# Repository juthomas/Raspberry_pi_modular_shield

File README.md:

# Raspberry Pi hat for modular synthesizer input

## Schematics

- [Link to pdf](https://github.com/juthomas/Raspberry_pi_modular_shield/blob/master/Schematics%20PDF/Modular_Shield.pdf)

## Bill Of Materials

- [Link to IBOM](https://juthomas.github.io/Raspberry_pi_modular_shield/)

## Components

- [10K Resistors](https://www.lcsc.com/product-detail/Chip-Resistor-Surface-Mount_UNI-ROYAL-Uniroyal-Elec-0603WAF1002T5E_C25804.html) C25804

- [Zener Diodes](https://www.lcsc.com/product-detail/Zener-Diodes_onsemi-SZMM5Z6V8T1G_C894569.html) C894569

- [MCP3008](https://www.lcsc.com/product-detail/Analog-To-Digital-Converters-ADCs_Microchip-Tech-MCP3008-I-SL_C1520159.html) C1520159

## Install dependency for C coding

[spidev-lib](https://github.com/juthomas/spidev-lib)

dont forget to add the `-lspidev-lib` flag when compiling

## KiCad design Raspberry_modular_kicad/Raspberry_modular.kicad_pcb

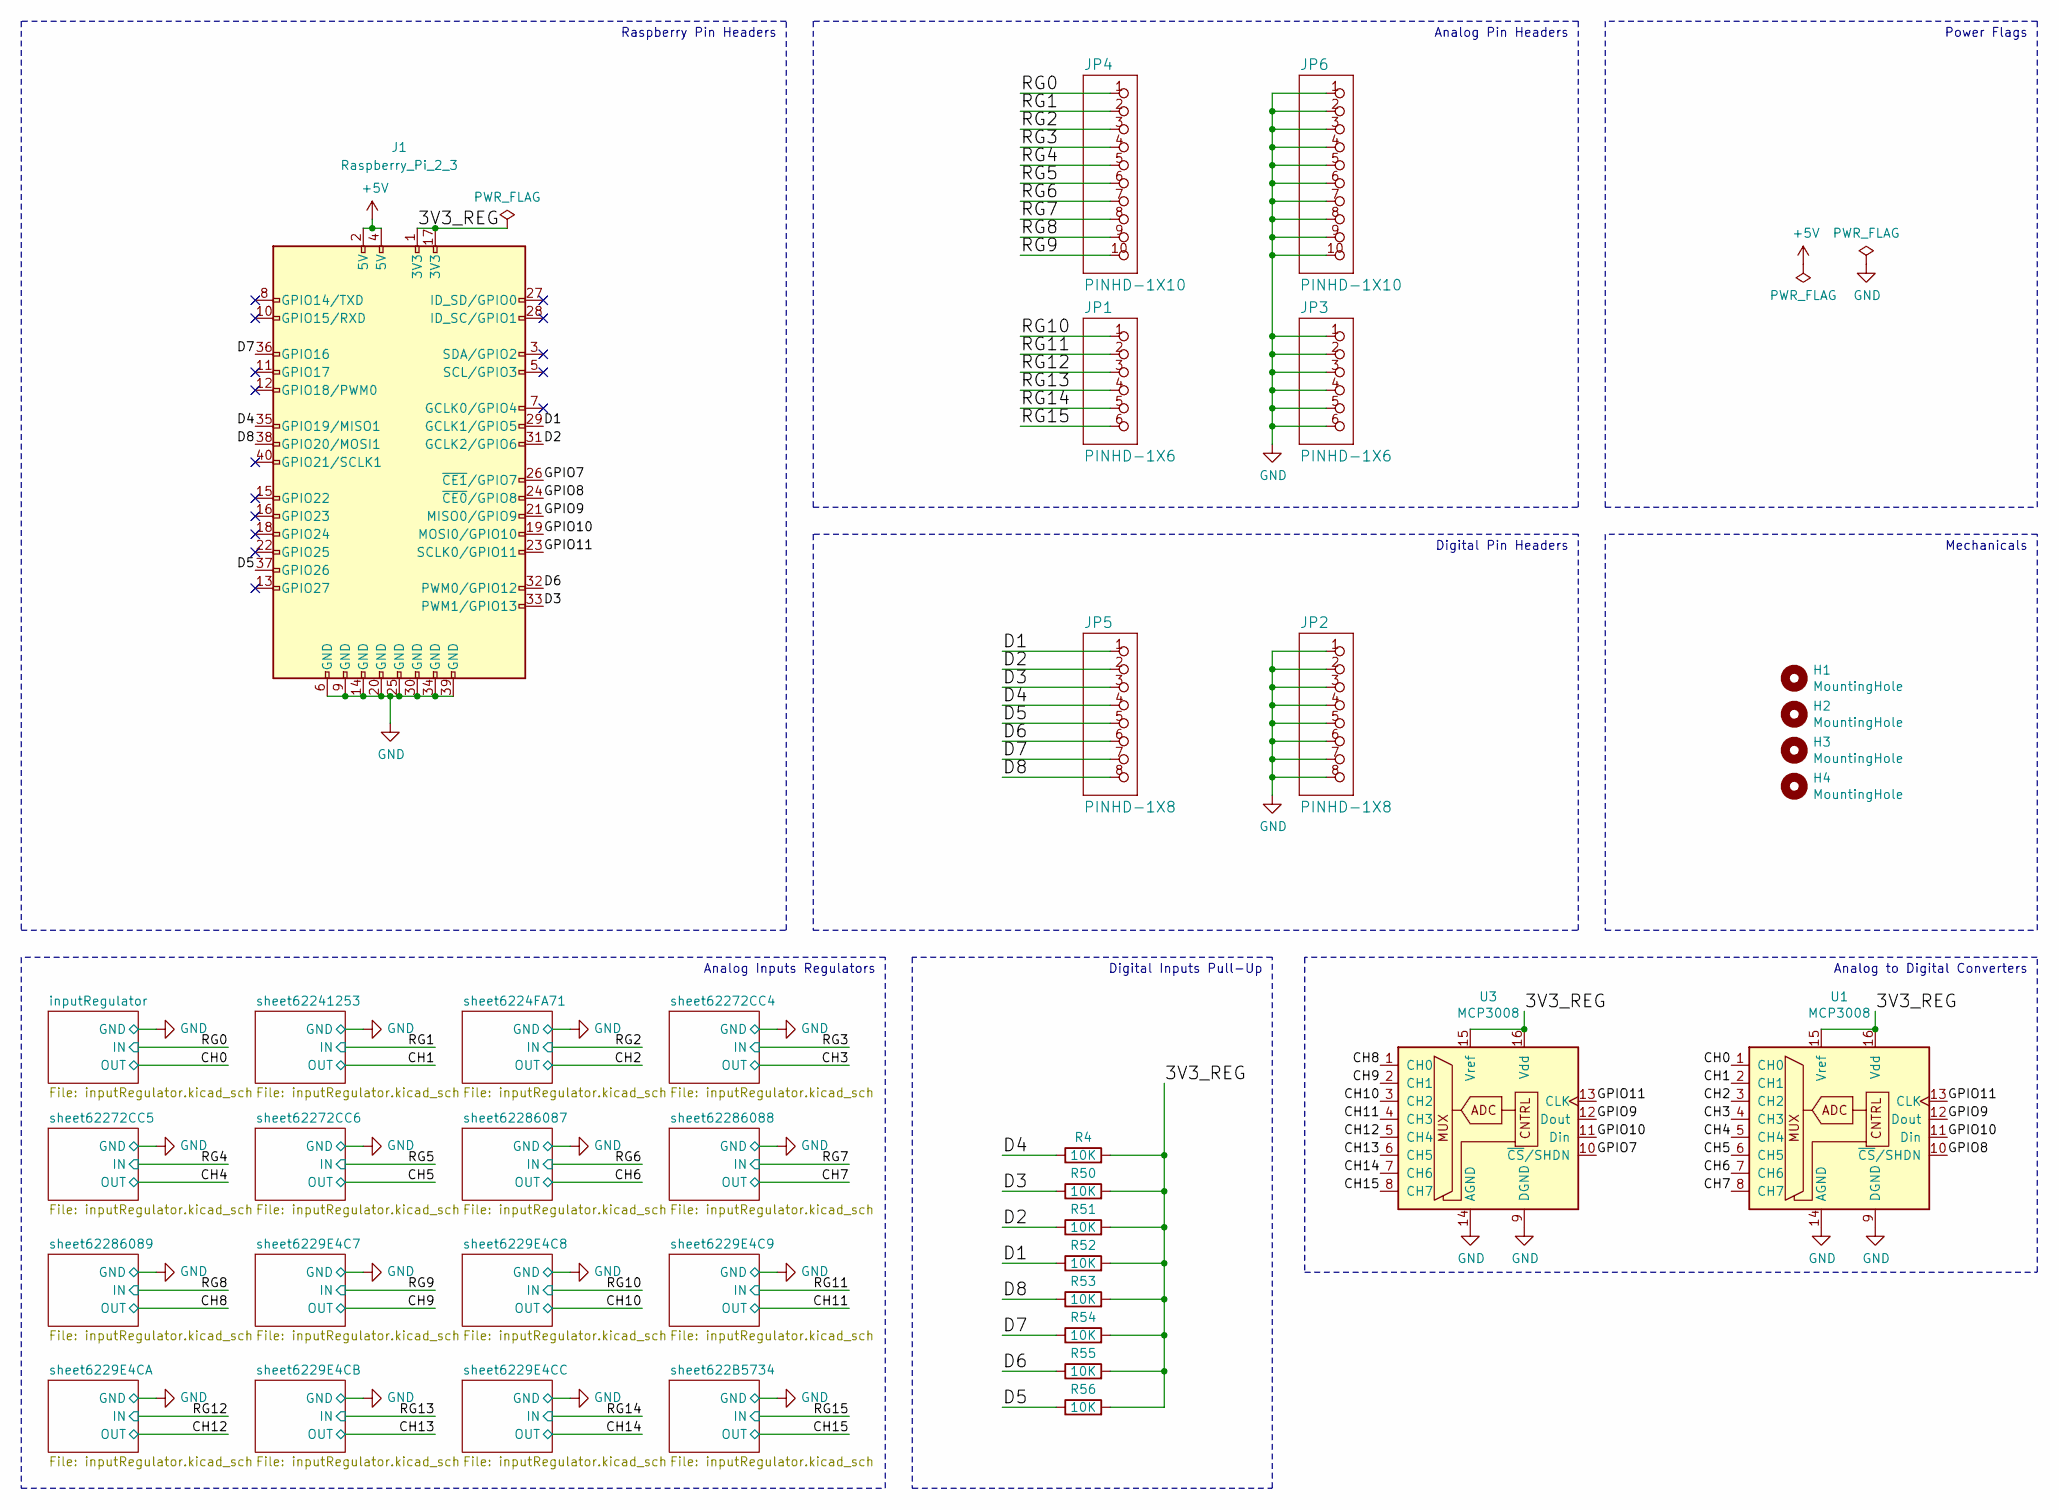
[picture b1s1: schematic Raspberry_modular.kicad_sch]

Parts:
H1, H2, H3, H4: MountingHole; MountingHole_2.7mm_M2.5
J1: Raspberry_Pi_2_3; PIN_20X2
JP1, JP3: PINHD-1X6; 1X06-BIG
JP2, JP5: PINHD-1X8; 1X08-BIG
JP4, JP6: PINHD-1X10; 1X10-BIG
R4, R50, R51, R52, R53, R54, R55, R56: 10K; R_0603_1608Metric; LCSC C25804
U1, U3: MCP3008; MCP3008 SOIC16; LCSC C1520159

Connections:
+5V: J1.2 (5V), J1.4 (5V)
/3V3_REG: J1.1 (3V3), J1.17 (3V3), R4.2, R50.2, R51.2, R52.2, R53.2, R54.2, R55.2, R56.2, U1.15 (Vref), U1.16 (Vdd), U3.15 (Vref), U3.16 (Vdd)
/CH0: U1.1 (CH0); also elsewhere on the board
/CH1: U1.2 (CH1); also elsewhere on the board
/CH2: U1.3 (CH2); also elsewhere on the board
/CH3: U1.4 (CH3); also elsewhere on the board
/CH4: U1.5 (CH4); also elsewhere on the board
/CH5: U1.6 (CH5); also elsewhere on the board
/CH6: U1.7 (CH6); also elsewhere on the board
/CH7: U1.8 (CH7); also elsewhere on the board
/CH8: U3.1 (CH0); also elsewhere on the board
/CH9: U3.2 (CH1); also elsewhere on the board
/CH10: U3.3 (CH2); also elsewhere on the board
/CH11: U3.4 (CH3); also elsewhere on the board
/CH12: U3.5 (CH4); also elsewhere on the board
/CH13: U3.6 (CH5); also elsewhere on the board
/CH14: U3.7 (CH6); also elsewhere on the board
/CH15: U3.8 (CH7); also elsewhere on the board
/D1: J1.29 (GCLK1/GPIO5), JP5.1, R52.1
/D2: J1.31 (GCLK2/GPIO6), JP5.2, R51.1
/D3: J1.33 (PWM1/GPIO13), JP5.3, R50.1
/D4: J1.35 (GPIO19/MISO1), JP5.4, R4.1
/D5: J1.37 (GPIO26), JP5.5, R56.1
/D6: J1.32 (PWM0/GPIO12), JP5.6, R55.1
/D7: J1.36 (GPIO16), JP5.7, R54.1
/D8: J1.38 (GPIO20/MOSI1), JP5.8, R53.1
/GPIO7: J1.26 (~CE1/GPIO7), U3.10 (~CS/SHDN)
/GPIO8: J1.24 (~CE0/GPIO8), U1.10 (~CS/SHDN)
/GPIO9: J1.21 (MISO0/GPIO9), U1.12 (Dout), U3.12 (Dout)
/GPIO10: J1.19 (MOSI0/GPIO10), U1.11 (Din), U3.11 (Din)
/GPIO11: J1.23 (SCLK0/GPIO11), U1.13 (CLK), U3.13 (CLK)
/RG0: JP4.1; also elsewhere on the board
/RG1: JP4.2; also elsewhere on the board
/RG2: JP4.3; also elsewhere on the board
/RG3: JP4.4; also elsewhere on the board
/RG4: JP4.5; also elsewhere on the board
/RG5: JP4.6; also elsewhere on the board
/RG6: JP4.7; also elsewhere on the board
/RG7: JP4.8; also elsewhere on the board
/RG8: JP4.9; also elsewhere on the board
/RG9: JP4.10; also elsewhere on the board
/RG10: JP1.1; also elsewhere on the board
/RG11: JP1.2; also elsewhere on the board
/RG12: JP1.3; also elsewhere on the board
/RG13: JP1.4; also elsewhere on the board
/RG14: JP1.5; also elsewhere on the board
/RG15: JP1.6; also elsewhere on the board
GND: J1.6 (GND), J1.9 (GND), J1.14 (GND), J1.20 (GND), J1.25 (GND), J1.30 (GND), J1.34 (GND), J1.39 (GND), JP2.1, JP2.2, JP2.3, JP2.4, JP2.5, JP2.6, JP2.7, JP2.8, JP3.1, JP3.2, JP3.3, JP3.4, JP3.5, JP3.6, JP6.1, JP6.2, JP6.3, JP6.4, JP6.5, JP6.6, JP6.7, JP6.8, JP6.9, JP6.10, U1.9 (DGND), U1.14 (AGND), U3.9 (DGND), U3.14 (AGND); also elsewhere on the board

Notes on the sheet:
Digital Inputs Pull-Up
Raspberry Pin Headers
Mechanicals
Analog Inputs Regulators
Digital Pin Headers
Analog Pin Headers
Analog to Digital Converters
Power Flags

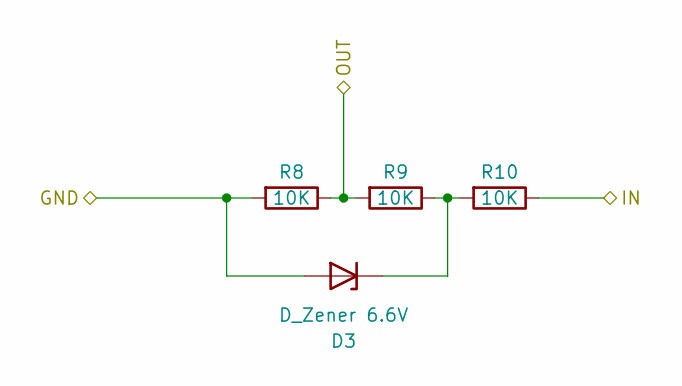
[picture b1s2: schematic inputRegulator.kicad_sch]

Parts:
D3: D_Zener 6.6V; D_0603_1608Metric; LCSC C894569
R8, R9, R10: 10K; R_0603_1608Metric; LCSC C25804

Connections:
/CH2: R8.1, R9.2; also elsewhere on the board
/RG2: R10.1; also elsewhere on the board
GND: D3.2 (A), R8.2; also elsewhere on the board
unnamed: D3.1 (K), R9.1, R10.2

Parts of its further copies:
D1, D2, D4, D5, D6, D7, D8, D9, D10, D11, D12, D13, D14, D15, D16: D_Zener 6.6V; D_0603_1608Metric; LCSC C894569
R1, R2, R3, R5, R6, R7, R11, R12, R13, R14, R15, R16, R17, R18, R19, R20, R21, R22, R23, R24, R25, R26, R27, R28, R29, R30, R31, R32, R33, R34, R35, R36, R37, R38, R39, R40, R41, R42, R43, R44, R45, R46, R47, R48, R49: 10K; R_0603_1608Metric; LCSC C25804

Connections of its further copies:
/CH0: R1.1, R2.2; also elsewhere on the board
/CH1: R5.1, R6.2; also elsewhere on the board
/CH3: R11.1, R12.2; also elsewhere on the board
/CH4: R14.1, R15.2; also elsewhere on the board
/CH5: R17.1, R18.2; also elsewhere on the board
/CH6: R20.1, R21.2; also elsewhere on the board
/CH7: R23.1, R24.2; also elsewhere on the board
/CH8: R26.1, R27.2; also elsewhere on the board
/CH9: R29.1, R30.2; also elsewhere on the board
/CH10: R32.1, R33.2; also elsewhere on the board
/CH11: R35.1, R36.2; also elsewhere on the board
/CH12: R38.1, R39.2; also elsewhere on the board
/CH13: R41.1, R42.2; also elsewhere on the board
/CH14: R44.1, R45.2; also elsewhere on the board
/CH15: R47.1, R48.2; also elsewhere on the board
/RG0: R3.1; also elsewhere on the board
/RG1: R7.1; also elsewhere on the board
/RG3: R13.1; also elsewhere on the board
/RG4: R16.1; also elsewhere on the board
/RG5: R19.1; also elsewhere on the board
/RG6: R22.1; also elsewhere on the board
/RG7: R25.1; also elsewhere on the board
/RG8: R28.1; also elsewhere on the board
/RG9: R31.1; also elsewhere on the board
/RG10: R34.1; also elsewhere on the board
/RG11: R37.1; also elsewhere on the board
/RG12: R40.1; also elsewhere on the board
/RG13: R43.1; also elsewhere on the board
/RG14: R46.1; also elsewhere on the board
/RG15: R49.1; also elsewhere on the board
GND: D1.2 (A), D2.2 (A), D4.2 (A), D5.2 (A), D6.2 (A), D7.2 (A), D8.2 (A), D9.2 (A), D10.2 (A), D11.2 (A), D12.2 (A), D13.2 (A), D14.2 (A), D15.2 (A), D16.2 (A), R1.2, R5.2, R11.2, R14.2, R17.2, R20.2, R23.2, R26.2, R29.2, R32.2, R35.2, R38.2, R41.2, R44.2, R47.2; also elsewhere on the board
unnamed: D1.1 (K), R2.1, R3.2
unnamed: D2.1 (K), R6.1, R7.2
unnamed: D4.1 (K), R12.1, R13.2
unnamed: D5.1 (K), R15.1, R16.2
unnamed: D6.1 (K), R18.1, R19.2
unnamed: D7.1 (K), R21.1, R22.2
unnamed: D8.1 (K), R24.1, R25.2
unnamed: D9.1 (K), R27.1, R28.2
unnamed: D10.1 (K), R30.1, R31.2
unnamed: D11.1 (K), R33.1, R34.2
unnamed: D12.1 (K), R36.1, R37.2
unnamed: D13.1 (K), R39.1, R40.2
unnamed: D14.1 (K), R42.1, R43.2
unnamed: D15.1 (K), R45.1, R46.2
unnamed: D16.1 (K), R48.1, R49.2

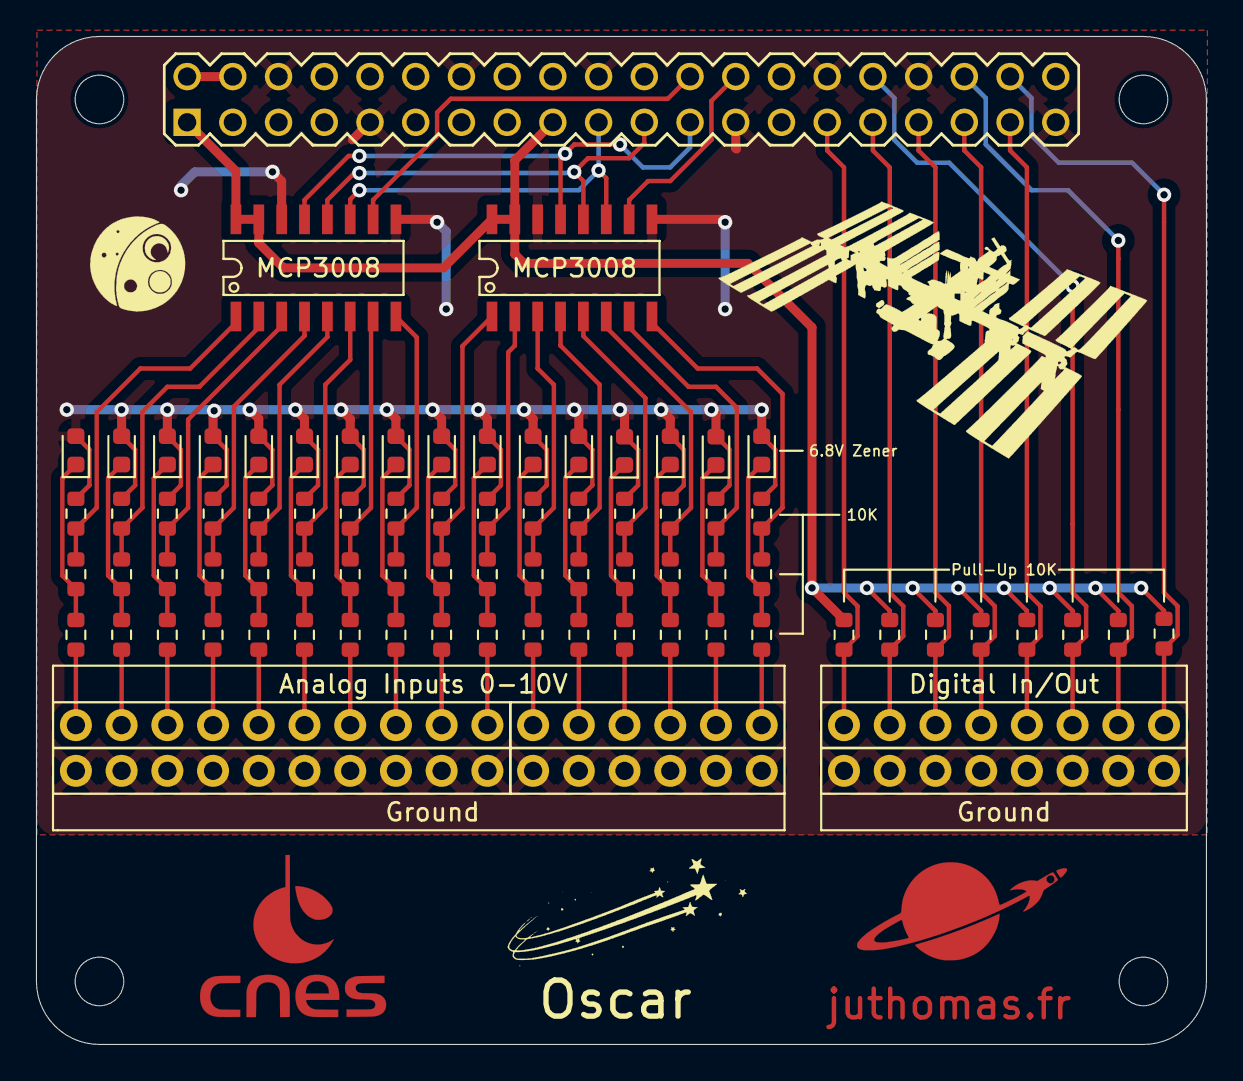
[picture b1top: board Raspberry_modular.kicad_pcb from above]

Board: 2 copper layers, 65.0 x 56.0 mm, 85 parts (0 on the bottom side), 64 nets.

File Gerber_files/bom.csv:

Designator,Footprint,Quantity,Value,LCSC Part #
"D1, D10, D11, D12, D13, D14, D15, D16, D2, D3, D4, D5, D6, D7, D8, D9",0603,16,D_Zener 6.6V,C894569
JP2,1X08-BIG,1,PINHD-1X8,
"R1, R10, R11, R12, R13, R14, R15, R16, R17, R18, R19, R2, R20, R21, R22, R23, R24, R25, R26, R27, R28, R29, R3, R30, R31, R32, R33, R34, R35, R36, R37, R38, R39, R4, R40, R41, R42, R43, R44, R45, R46, R47, R48, R49, R5, R50, R51, R52, R53, R54, R55, R56, R6, R7, R8, R9",0603,56,10K,C25804
"U1, U3",MCP3008 SOIC16,2,MCP3008,C1520159

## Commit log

2021-12-10 [INIT] Kicad fonctionnal
2021-12-11 [ADD] Readme + images
2021-12-11 [UPDT] README
2021-12-12 [ADD] Gerber files
2022-01-06 [ADD] Shield Code example
2022-01-06 [ADD] Dependency link to readme
2022-01-06 [UPDT] Readme links
2022-01-06 [ADD] Error message for open fd failed
2023-11-12 [ERC] Fix problems by creating new libs
2023-11-12 [UDPT] Makefile
2023-11-12 [UDPT] All symbols are now in lib
2023-11-12 [UDPT] Inputs on schematics
2023-11-12 [FIX] Connection problems
2023-11-12 [UDPT] Shematics
2023-11-12 [FIX] Missing annotations
2023-11-13 [UDPT] Electricals footprints
2023-11-13 [DRC] Problems fixed
2023-11-13 [UDPT] Filled Zones
2023-11-13 [ADD] 2x20 Socket 3d
2023-11-13 [ADD] Bom
2023-11-13 [ADD] IBOM
2023-11-13 [FIX] Some productions problems
2023-11-13 [FIX] Production build
2023-11-13 [ADD] Production build with updated Silk
2023-11-13 [UDPT] IBOM
2023-11-13 [ADD] Schematics PDFs
2023-11-13 [UDPT] Kicad Project name
2023-11-13 [CLEAN] Removed Useless files/folders
2023-11-13 [FIX] Build production
2023-11-13 [UDPT] Readme
2023-11-13 [UDPT] Schematics PDFs
2023-11-13 [FIX] Missing Text On IBOM
2023-11-14 [RM] Misspelled folder
2023-11-15 [CLEAN] Remove useless files & update Readme
2023-11-27 [UDPT] Mounting Holes Upgraded
